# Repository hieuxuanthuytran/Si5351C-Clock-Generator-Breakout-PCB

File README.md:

# Si5351C-Clock-Generator-Breakout-PCB
Electrical schematic and PCB layout files for the Si5351C Clock Generator Breakout

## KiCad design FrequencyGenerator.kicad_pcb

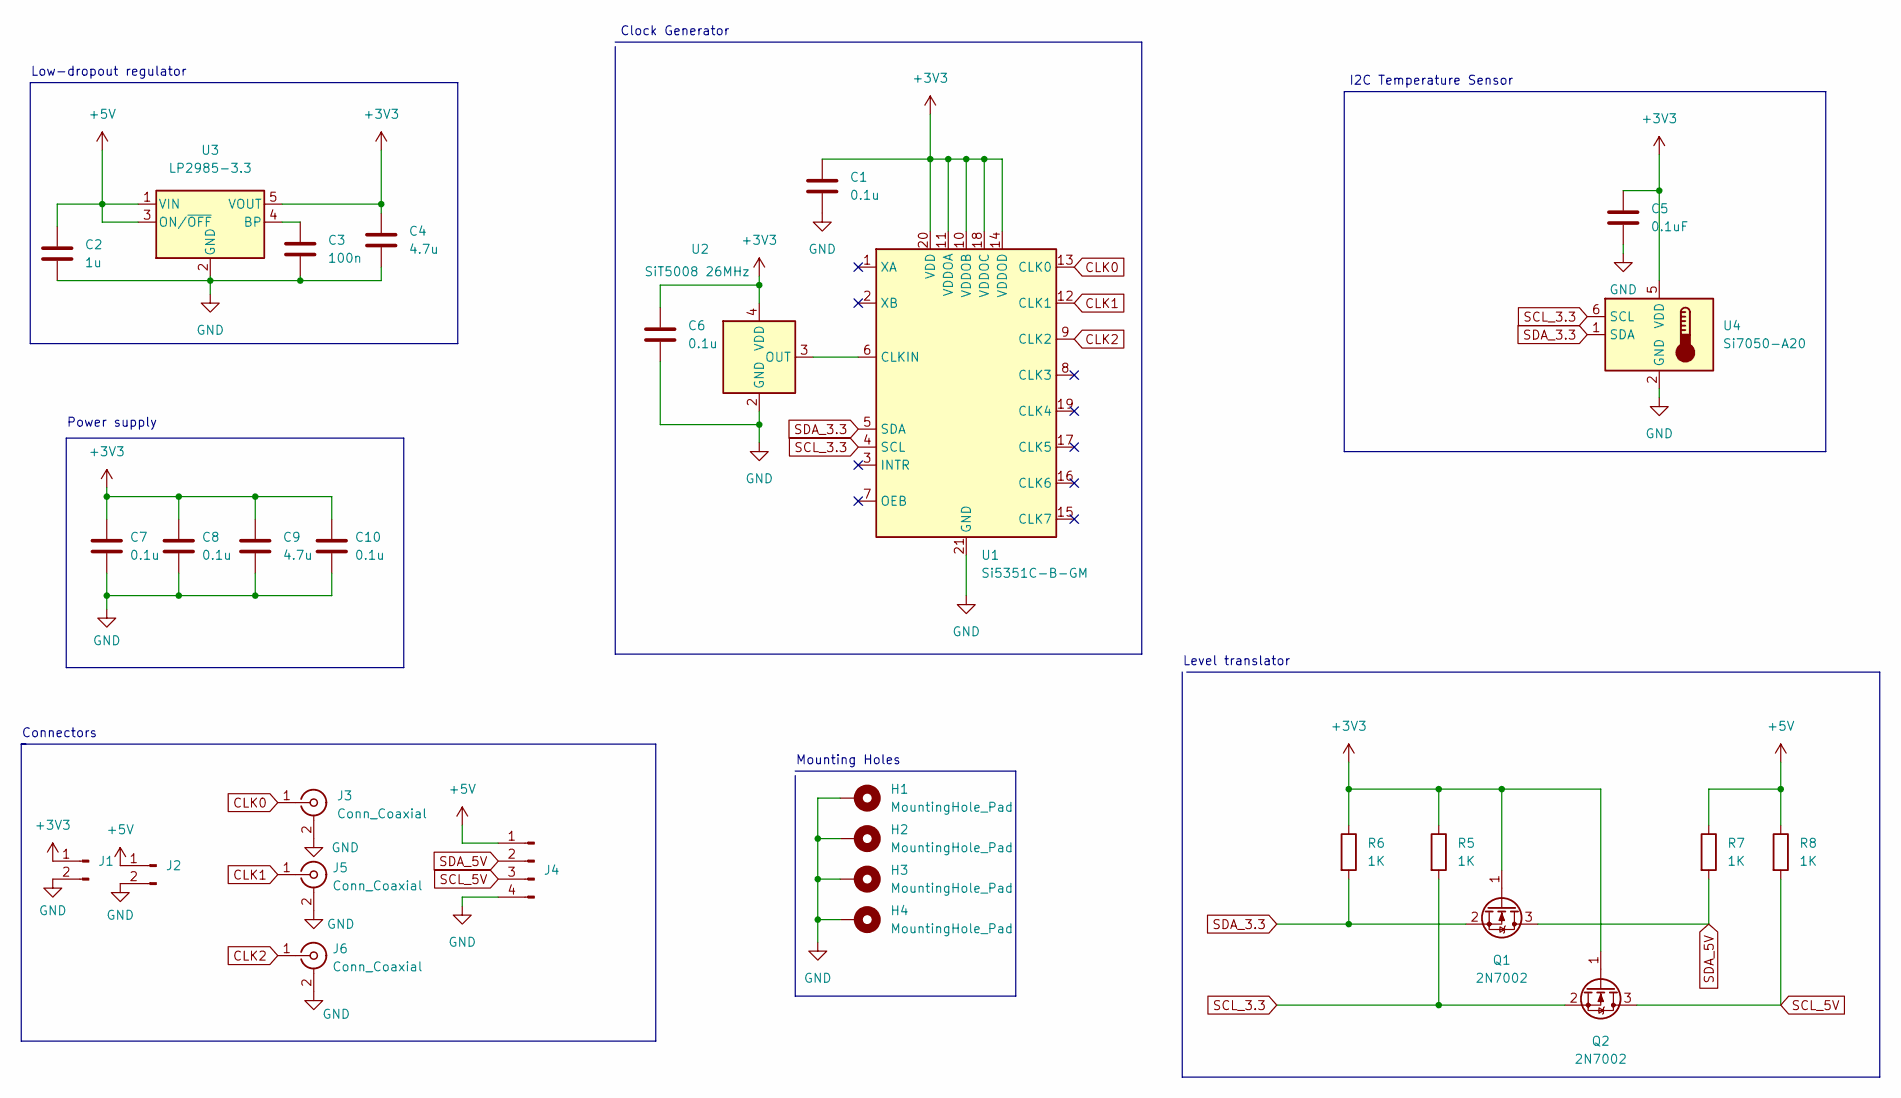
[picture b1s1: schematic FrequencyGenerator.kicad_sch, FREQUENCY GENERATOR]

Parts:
C1, C6, C7, C8, C10: 0.1u; C_0402_1005Metric
C2: 1u; C_0402_1005Metric
C3: 100n; C_0402_1005Metric
C4, C9: 4.7u; C_0402_1005Metric
C5: 0.1uF; C_0402_1005Metric
H1, H2, H3, H4: MountingHole_Pad; MountingHole_2.5mm_Pad
J1, J2: Conn_01x02_Male; PinHeader_1x02_P2.54mm_Vertical
J3, J5, J6: Conn_Coaxial; SMA_Samtec_SMA-J-P-X-ST-EM1_EdgeMount
J4: Conn_01x04_Male; PinHeader_1x04_P2.54mm_Vertical
Q1, Q2: 2N7002; SOT-23
R5, R6, R7, R8: 1K; R_0603_1608Metric
U1: Si5351C-B-GM; Silicon_Labs-Si5351C-B-GM-Level_C
U2: SiT5008 26MHz; Oscillator_SMD_Kyocera_KC2520Z-4Pin_2.5x2.0mm
U3: LP2985-3.3; SOT-23-5
U4: Si7050-A20; DFN-6-1EP_3x3mm_P1mm_EP1.5x2.4mm

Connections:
+3V3: C1.1, C4.1, C5.1, C6.1, C7.2, C8.1, C9.1, C10.1, J1.1, Q1.1 (G), Q2.1 (G), R5.1, R6.1, U1.10 (VDDOB), U1.11 (VDDOA), U1.14 (VDDOD), U1.18 (VDDOC), U1.20 (VDD), U2.4 (VDD), U3.5 (VOUT), U4.5 (VDD)
+5V: C2.2, J2.1, J4.1, R7.1, R8.1, U3.1 (VIN), U3.3 (ON/~OFF)
CLK0: J3.1 (In), U1.13 (CLK0)
CLK1: J5.1 (In), U1.12 (CLK1)
CLK2: J6.1 (In), U1.9 (CLK2)
GND: C1.2, C2.1, C3.2, C4.2, C5.2, C6.2, C7.1, C8.2, C9.2, C10.2, H1.1, H2.1, H3.1, H4.1, J1.2, J2.2, J3.2 (Ext), J4.4, J5.2 (Ext), J6.2 (Ext), U1.21 (GND), U1.~, U2.2 (GND), U3.2 (GND), U4.2 (GND)
unnamed: C3.1, U3.4 (BP)
unnamed: U1.6 (CLKIN), U2.3 (OUT)
SCL_3.3: Q2.2 (S), R5.2, U1.4 (SCL), U4.6 (SCL)
SCL_5V: J4.3, Q2.3 (D), R8.2
SDA_3.3: Q1.2 (S), R6.2, U1.5 (SDA), U4.1 (SDA)
SDA_5V: J4.2, Q1.3 (D), R7.2

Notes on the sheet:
Level translator
Connectors
Low-dropout regulator
Clock Generator
Power supply
Mounting Holes
I2C Temperature Sensor

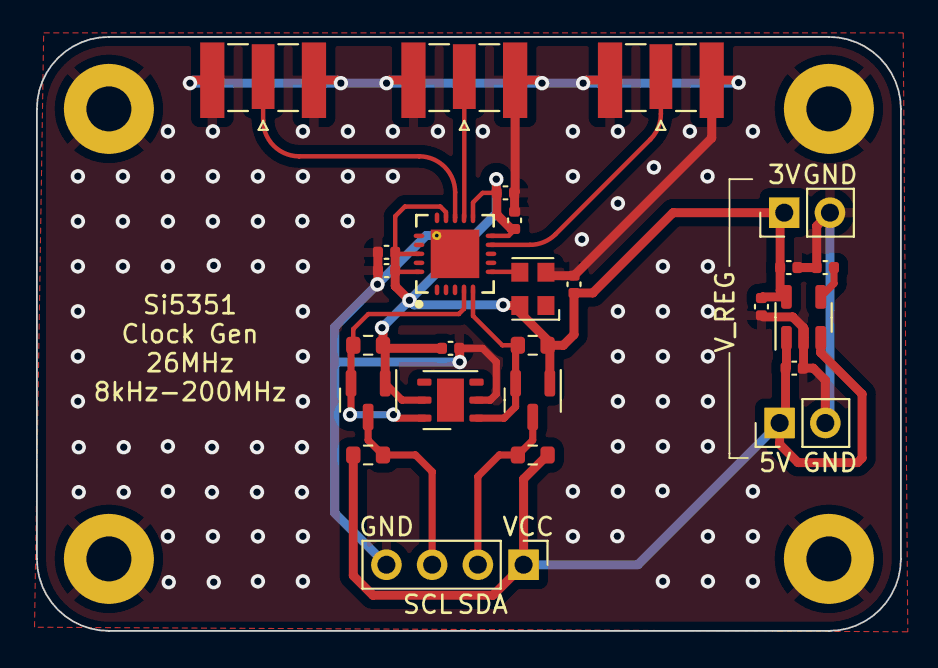
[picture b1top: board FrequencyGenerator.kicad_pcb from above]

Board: 2 copper layers, 48.0 x 33.0 mm, 30 parts (0 on the bottom side), 12 nets.
